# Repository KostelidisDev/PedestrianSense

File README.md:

# PedestrianSense

Development of an automatic traffic light with pedestrian detection using Arduino, distance sensors, LEDs and an audible
signal, with automatic adjustment transition in case of presence or absence of pedestrians.

# Description

This work focuses on the development of an automatic signaling system that detects the presence of pedestrians and
adjusts the state of the traffic lights accordingly. The system uses the Arduino Uno microcontroller, ultrasonic sensors
for pedestrian detection, LEDs for the traffic lights and a buzzer for the audible notification when pedestrians are
detected. The goal of the implementation is to reduce unnecessary waiting times, ensuring that drivers do not wait
unnecessarily when there are no pedestrians wishing to cross the road and that pedestrians will have priority to cross
the road.

# Design

[Tinker This](https://www.tinkercad.com/things/7rupZ55A2RG-pedestriansense?sharecode=2-Y8UZJDhC64ENvKhkmB4mk3aNhrKVhh2EfPOBmN8SA)

# Extra files
** The extra files are written in Greek Language.
* [PDF/Text](./assets/PedestrianSense.pdf)
* [PowerPoint/Presentation](./assets/PedestrianSense.pptx)
* [MOV/Demo](./assets/PedestrianSense.mov)

# License

[MIT License](./LICENSE)

# Disclaimer

This project was conducted as part of the course Ρ101: Embedded Systems in the M.Sc. program in Robotics, offered by the
Department of Computer, Informatics and Telecommunications Engineering at the International Hellenic University.

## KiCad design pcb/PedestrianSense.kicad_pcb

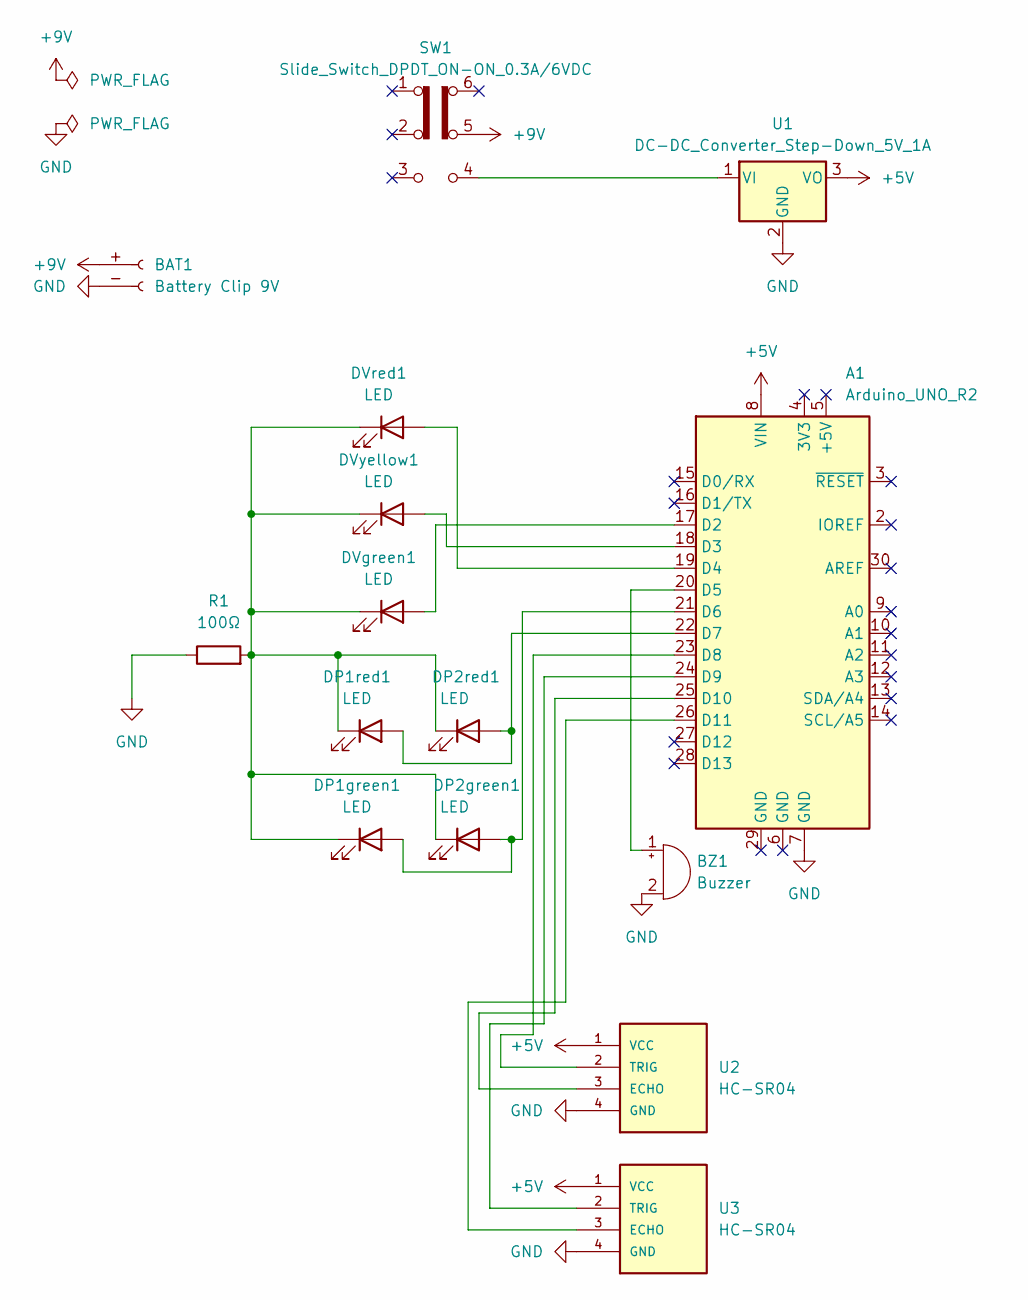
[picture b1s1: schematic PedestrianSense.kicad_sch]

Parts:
A1: Arduino_UNO_R2
BAT1: Battery Clip 9V; Battery_Clip_9V
BZ1: Buzzer; Buzzer_D14mm_H7mm_P10mm
DP1green1, DP1red1, DP2green1, DP2red1: LED; LED_D2.0mm_W4.8mm_H2.5mm_FlatTop
DVgreen1: LED; LED_D2.0mm_W4.8mm_H2.5mm_FlatTop
DVred1: LED; LED_D2.0mm_W4.8mm_H2.5mm_FlatTop
DVyellow1: LED; LED_D2.0mm_W4.8mm_H2.5mm_FlatTop
R1: 100Ω; R_Axial_DIN0204_L3.6mm_D1.6mm_P7.62mm_Horizontal
SW1: Slide_Switch_DPDT_ON-ON_0.3A/6VDC; SW_CK_JS202011CQN_DPDT_Straight
U1: DC-DC_Converter_Step-Down_5V_1A; TO-220-3_Vertical
U2, U3: HC-SR04; XCVR_HC-SR04

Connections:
+5V: A1.8 (VIN), U1.3 (VO), U2.1 (VCC), U3.1 (VCC)
+9V: BAT1.+ (Pin_1), SW1.5 (B)
GND: A1.7 (GND), BAT1.- (Pin_2), BZ1.2 (-), R1.1, U1.2 (GND), U2.4 (GND), U3.4 (GND)
unnamed: A1.17 (D2), DVgreen1.2 (A)
unnamed: A1.18 (D3), DVyellow1.2 (A)
unnamed: A1.19 (D4), DVred1.2 (A)
unnamed: A1.20 (D5), BZ1.1 (+)
unnamed: A1.21 (D6), DP1green1.2 (A), DP2green1.2 (A)
unnamed: A1.22 (D7), DP1red1.2 (A), DP2red1.2 (A)
unnamed: A1.23 (D8), U2.2 (TRIG)
unnamed: A1.24 (D9), U3.2 (TRIG)
unnamed: A1.25 (D10), U2.3 (ECHO)
unnamed: A1.26 (D11), U3.3 (ECHO)
unnamed: DP1green1.1 (K), DP1red1.1 (K), DP2green1.1 (K), DP2red1.1 (K), DVgreen1.1 (K), DVred1.1 (K), DVyellow1.1 (K), R1.2
unnamed: SW1.4 (A), U1.1 (VI)

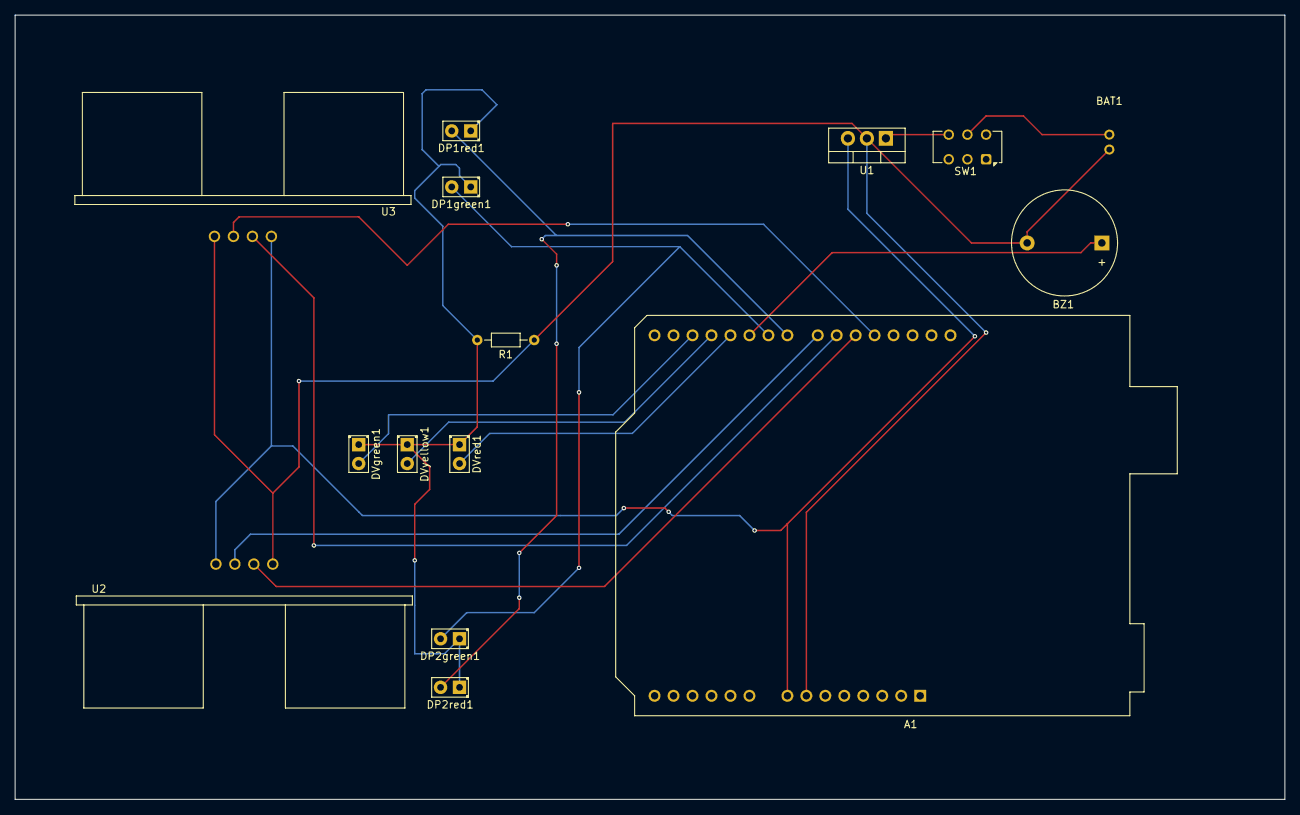
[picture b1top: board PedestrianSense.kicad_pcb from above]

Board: 2 copper layers, 170.0 x 105.0 mm, 15 parts (0 on the bottom side), 15 nets.

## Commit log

2024-11-25 add github repo link and qr for tinkercad project on presentation
2024-11-25 remove .DS_Store files
2024-11-26 add demo video
2024-11-26 add demo video to README.md
2025-01-06 add KiCad project (schematic and pcb)
